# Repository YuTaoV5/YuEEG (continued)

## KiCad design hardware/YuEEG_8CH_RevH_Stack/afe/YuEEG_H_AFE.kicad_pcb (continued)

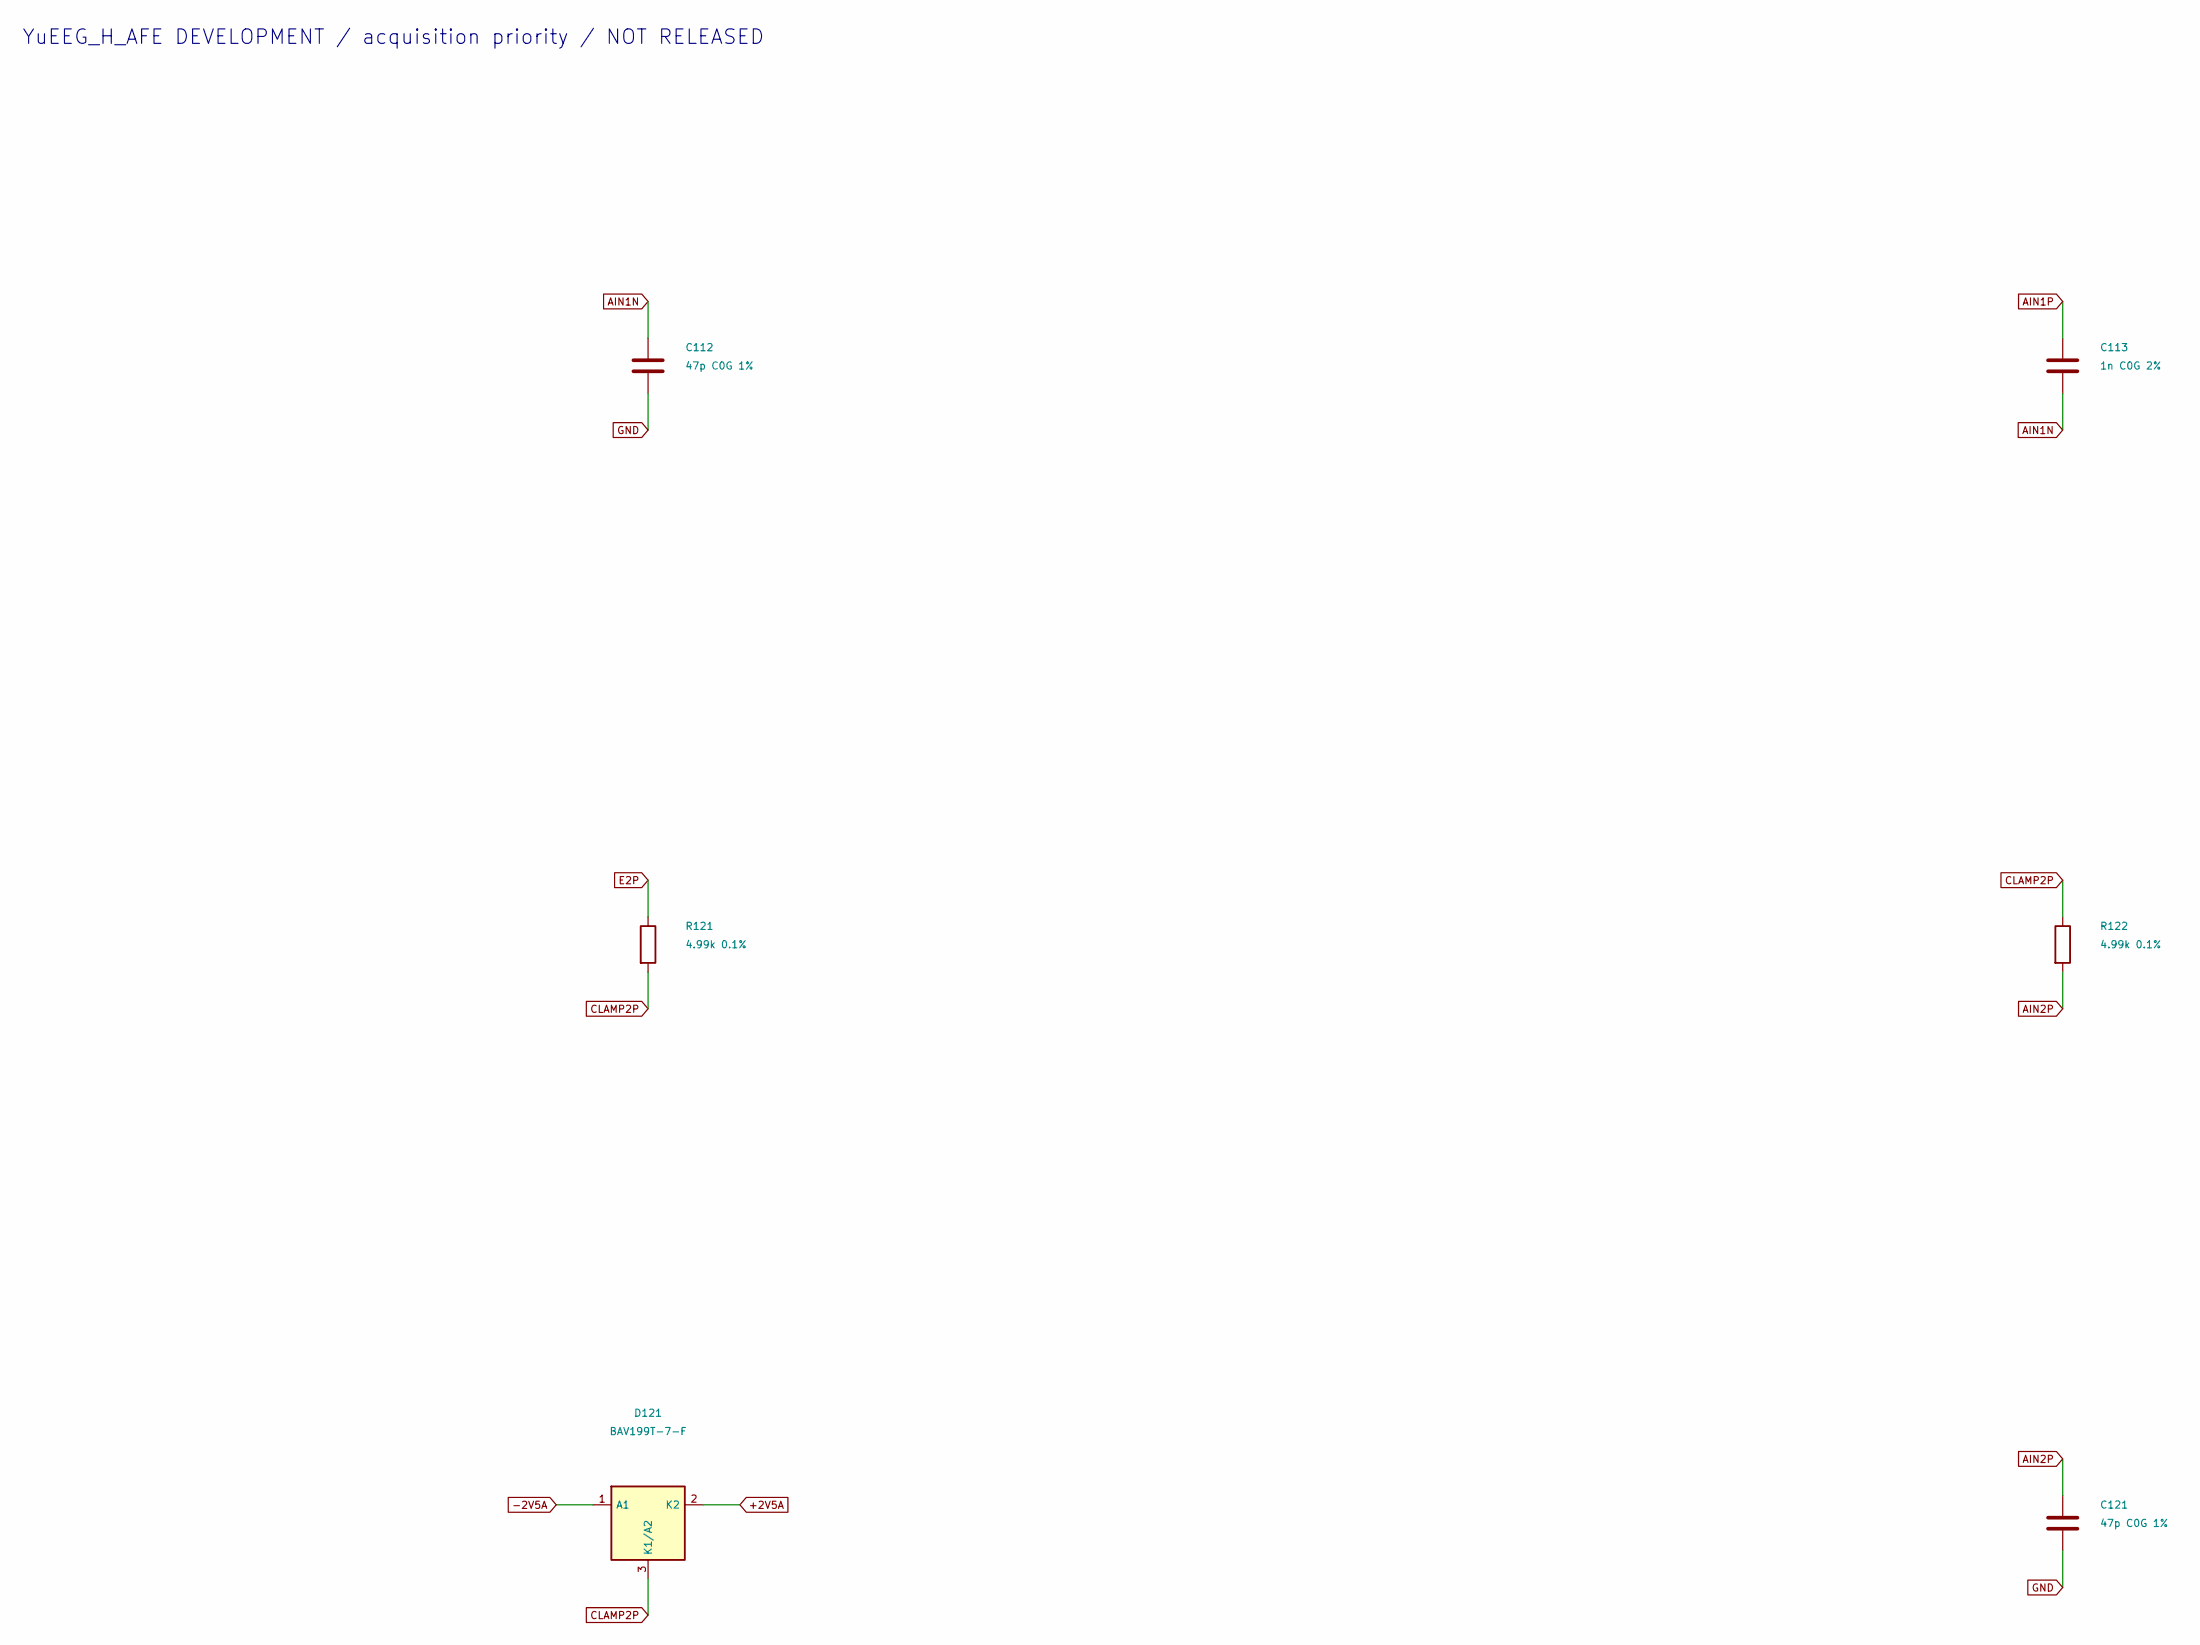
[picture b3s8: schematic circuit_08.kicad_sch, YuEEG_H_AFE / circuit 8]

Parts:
C112, C121: 47p C0G 1%; C_0402_1005Metric
C113: 1n C0G 2%; C_0402_1005Metric
D121: BAV199T-7-F; SOT-523
R121, R122: 4.99k 0.1%; R_0402_1005Metric

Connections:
+2V5A: D121.2 (K2); also elsewhere on the board
-2V5A: D121.1 (A1); also elsewhere on the board
AIN1N: C112.1, C113.2; also elsewhere on the board
AIN1P: C113.1; also elsewhere on the board
AIN2P: C121.1, R122.2; also elsewhere on the board
CLAMP2P: D121.3 (K1/A2), R121.2, R122.1
E2P: R121.1; also elsewhere on the board
GND: C112.2, C121.2; also elsewhere on the board

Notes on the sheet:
YuEEG_H_AFE DEVELOPMENT / acquisition priority / NOT RELEASED

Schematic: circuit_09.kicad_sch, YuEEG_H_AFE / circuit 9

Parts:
C122: 47p C0G 1%; C_0402_1005Metric
C123: 1n C0G 2%; C_0402_1005Metric
D122: BAV199T-7-F; SOT-523
R123, R124, R131: 4.99k 0.1%; R_0402_1005Metric

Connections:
+2V5A: D122.2 (K2); also elsewhere on the board
-2V5A: D122.1 (A1); also elsewhere on the board
AIN2N: C122.1, C123.2, R124.2; also elsewhere on the board
AIN2P: C123.1; also elsewhere on the board
CLAMP2N: D122.3 (K1/A2), R123.2, R124.1
CLAMP3P: R131.2; also elsewhere on the board
E3P: R131.1; also elsewhere on the board
GND: C122.2; also elsewhere on the board
REF_RAW: R123.1; also elsewhere on the board

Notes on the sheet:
YuEEG_H_AFE DEVELOPMENT / acquisition priority / NOT RELEASED

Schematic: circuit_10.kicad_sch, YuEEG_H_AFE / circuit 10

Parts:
C131: 47p C0G 1%; C_0402_1005Metric
D131, D132: BAV199T-7-F; SOT-523
R132, R133, R134: 4.99k 0.1%; R_0402_1005Metric

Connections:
+2V5A: D131.2 (K2), D132.2 (K2); also elsewhere on the board
-2V5A: D131.1 (A1), D132.1 (A1); also elsewhere on the board
AIN3N: R134.2; also elsewhere on the board
AIN3P: C131.1, R132.2; also elsewhere on the board
CLAMP3N: D132.3 (K1/A2), R133.2, R134.1
CLAMP3P: D131.3 (K1/A2), R132.1; also elsewhere on the board
GND: C131.2; also elsewhere on the board
REF_RAW: R133.1; also elsewhere on the board

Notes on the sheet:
YuEEG_H_AFE DEVELOPMENT / acquisition priority / NOT RELEASED

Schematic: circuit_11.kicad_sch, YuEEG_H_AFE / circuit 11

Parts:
C132, C141: 47p C0G 1%; C_0402_1005Metric
C133: 1n C0G 2%; C_0402_1005Metric
D141: BAV199T-7-F; SOT-523
R141, R142: 4.99k 0.1%; R_0402_1005Metric

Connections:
+2V5A: D141.2 (K2); also elsewhere on the board
-2V5A: D141.1 (A1); also elsewhere on the board
AIN3N: C132.1, C133.2; also elsewhere on the board
AIN3P: C133.1; also elsewhere on the board
AIN4P: C141.1, R142.2; also elsewhere on the board
CLAMP4P: D141.3 (K1/A2), R141.2, R142.1
E4P: R141.1; also elsewhere on the board
GND: C132.2, C141.2; also elsewhere on the board

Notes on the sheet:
YuEEG_H_AFE DEVELOPMENT / acquisition priority / NOT RELEASED

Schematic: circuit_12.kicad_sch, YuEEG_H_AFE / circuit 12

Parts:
C142: 47p C0G 1%; C_0402_1005Metric
C143: 1n C0G 2%; C_0402_1005Metric
D142: BAV199T-7-F; SOT-523
R143, R144, R151: 4.99k 0.1%; R_0402_1005Metric

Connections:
+2V5A: D142.2 (K2); also elsewhere on the board
-2V5A: D142.1 (A1); also elsewhere on the board
AIN4N: C142.1, C143.2, R144.2; also elsewhere on the board
AIN4P: C143.1; also elsewhere on the board
CLAMP4N: D142.3 (K1/A2), R143.2, R144.1
CLAMP5P: R151.2; also elsewhere on the board
E5P: R151.1; also elsewhere on the board
GND: C142.2; also elsewhere on the board
REF_RAW: R143.1; also elsewhere on the board

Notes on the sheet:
YuEEG_H_AFE DEVELOPMENT / acquisition priority / NOT RELEASED

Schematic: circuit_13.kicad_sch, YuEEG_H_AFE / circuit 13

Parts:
C151: 47p C0G 1%; C_0402_1005Metric
D151, D152: BAV199T-7-F; SOT-523
R152, R153, R154: 4.99k 0.1%; R_0402_1005Metric

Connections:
+2V5A: D151.2 (K2), D152.2 (K2); also elsewhere on the board
-2V5A: D151.1 (A1), D152.1 (A1); also elsewhere on the board
AIN5N: R154.2; also elsewhere on the board
AIN5P: C151.1, R152.2; also elsewhere on the board
CLAMP5N: D152.3 (K1/A2), R153.2, R154.1
CLAMP5P: D151.3 (K1/A2), R152.1; also elsewhere on the board
GND: C151.2; also elsewhere on the board
REF_RAW: R153.1; also elsewhere on the board

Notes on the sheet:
YuEEG_H_AFE DEVELOPMENT / acquisition priority / NOT RELEASED

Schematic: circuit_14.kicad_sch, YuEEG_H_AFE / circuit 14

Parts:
C152, C161: 47p C0G 1%; C_0402_1005Metric
C153: 1n C0G 2%; C_0402_1005Metric
D161: BAV199T-7-F; SOT-523
R161, R162: 4.99k 0.1%; R_0402_1005Metric

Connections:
+2V5A: D161.2 (K2); also elsewhere on the board
-2V5A: D161.1 (A1); also elsewhere on the board
AIN5N: C152.1, C153.2; also elsewhere on the board
AIN5P: C153.1; also elsewhere on the board
AIN6P: C161.1, R162.2; also elsewhere on the board
CLAMP6P: D161.3 (K1/A2), R161.2, R162.1
E6P: R161.1; also elsewhere on the board
GND: C152.2, C161.2; also elsewhere on the board

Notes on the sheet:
YuEEG_H_AFE DEVELOPMENT / acquisition priority / NOT RELEASED

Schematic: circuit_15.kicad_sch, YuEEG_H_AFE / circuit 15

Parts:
C162: 47p C0G 1%; C_0402_1005Metric
C163: 1n C0G 2%; C_0402_1005Metric
D162: BAV199T-7-F; SOT-523
R163, R164, R171: 4.99k 0.1%; R_0402_1005Metric

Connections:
+2V5A: D162.2 (K2); also elsewhere on the board
-2V5A: D162.1 (A1); also elsewhere on the board
AIN6N: C162.1, C163.2, R164.2; also elsewhere on the board
AIN6P: C163.1; also elsewhere on the board
CLAMP6N: D162.3 (K1/A2), R163.2, R164.1
CLAMP7P: R171.2; also elsewhere on the board
E7P: R171.1; also elsewhere on the board
GND: C162.2; also elsewhere on the board
REF_RAW: R163.1; also elsewhere on the board

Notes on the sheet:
YuEEG_H_AFE DEVELOPMENT / acquisition priority / NOT RELEASED

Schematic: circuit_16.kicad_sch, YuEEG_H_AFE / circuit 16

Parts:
C171: 47p C0G 1%; C_0402_1005Metric
D171, D172: BAV199T-7-F; SOT-523
R172, R173, R174: 4.99k 0.1%; R_0402_1005Metric

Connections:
+2V5A: D171.2 (K2), D172.2 (K2); also elsewhere on the board
-2V5A: D171.1 (A1), D172.1 (A1); also elsewhere on the board
AIN7N: R174.2; also elsewhere on the board
AIN7P: C171.1, R172.2; also elsewhere on the board
CLAMP7N: D172.3 (K1/A2), R173.2, R174.1
CLAMP7P: D171.3 (K1/A2), R172.1; also elsewhere on the board
GND: C171.2; also elsewhere on the board
REF_RAW: R173.1; also elsewhere on the board

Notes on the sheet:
YuEEG_H_AFE DEVELOPMENT / acquisition priority / NOT RELEASED

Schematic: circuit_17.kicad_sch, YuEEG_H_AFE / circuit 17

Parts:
C172, C181: 47p C0G 1%; C_0402_1005Metric
C173: 1n C0G 2%; C_0402_1005Metric
D181: BAV199T-7-F; SOT-523
R181, R182: 4.99k 0.1%; R_0402_1005Metric

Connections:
+2V5A: D181.2 (K2); also elsewhere on the board
-2V5A: D181.1 (A1); also elsewhere on the board
AIN7N: C172.1, C173.2; also elsewhere on the board
AIN7P: C173.1; also elsewhere on the board
AIN8P: C181.1, R182.2; also elsewhere on the board
CLAMP8P: D181.3 (K1/A2), R181.2, R182.1
E8P: R181.1; also elsewhere on the board
GND: C172.2, C181.2; also elsewhere on the board

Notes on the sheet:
YuEEG_H_AFE DEVELOPMENT / acquisition priority / NOT RELEASED

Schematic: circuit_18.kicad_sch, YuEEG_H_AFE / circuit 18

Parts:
C182: 47p C0G 1%; C_0402_1005Metric
C183: 1n C0G 2%; C_0402_1005Metric
C401: 22u 25V X7R; C_1206_3216Metric
D182: BAV199T-7-F; SOT-523
R183, R184: 4.99k 0.1%; R_0402_1005Metric

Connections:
+2V5A: D182.2 (K2); also elsewhere on the board
-2V5A: D182.1 (A1); also elsewhere on the board
AIN8N: C182.1, C183.2, R184.2; also elsewhere on the board
AIN8P: C183.1; also elsewhere on the board
CLAMP8N: D182.3 (K1/A2), R183.2, R184.1
GND: C182.2, C401.2; also elsewhere on the board
REF_RAW: R183.1; also elsewhere on the board
SYS_5V: C401.1; also elsewhere on the board

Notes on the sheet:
YuEEG_H_AFE DEVELOPMENT / acquisition priority / NOT RELEASED

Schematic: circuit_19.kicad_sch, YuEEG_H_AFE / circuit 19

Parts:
C402: 22u 25V X7R; C_1206_3216Metric
C403, C404: 10n C0G; C_0402_1005Metric
R401: 27.4k 0.1%; R_0402_1005Metric
R402: 10k 0.1%; R_0402_1005Metric
U401: TPS7A4901DGNR; HVSSOP-8-1EP_3x3mm_P0.65mm_EP1.57x1.89mm

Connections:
+4V4_PRE: C404.1, R401.1, U401.1 (OUT); also elsewhere on the board
GND: C402.2, C403.2, R402.2, U401.4 (GND), U401.9 (EP); also elsewhere on the board
LDO_FB: C404.2, R401.2, R402.1, U401.2 (FB)
LDO_NR: C403.1, U401.6 (NR/SS)
SYS_5V: C402.1, U401.5 (EN), U401.8 (IN); also elsewhere on the board

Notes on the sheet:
YuEEG_H_AFE DEVELOPMENT / acquisition priority / NOT RELEASED

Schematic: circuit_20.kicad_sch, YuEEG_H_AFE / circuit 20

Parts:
C405: 22u 16V X7R MSASE31LBB7226MTNA01; TY_MSASE31LBB7226MTNA01_1206
C410: 1u 10V X7R; C_0603_1608Metric
C411: 10n C0G; C_0402_1005Metric
D403: BAT46W pre-LDO reverse bypass; D_SOD-123
TP403: +4V4_PRE; TestPoint_Pad_D1.5mm
U403: TPS73225DBVR; SOT-23-5

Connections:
+2V5A: U403.5 (OUT); also elsewhere on the board
+4V4_PRE: C405.1, C410.1, D403.2 (A), TP403.1, U403.1 (IN), U403.3 (EN); also elsewhere on the board
GND: C405.2, C410.2, C411.2, U403.2 (GND); also elsewhere on the board
POS_NR: C411.1, U403.4 (NR)
SYS_5V: D403.1 (K); also elsewhere on the board

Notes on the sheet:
YuEEG_H_AFE DEVELOPMENT / acquisition priority / NOT RELEASED

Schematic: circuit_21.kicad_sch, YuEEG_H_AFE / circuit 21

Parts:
C412, C415: 10u 10V X7R; C_0805_2012Metric
C413, C414: 2.2u 10V X7R; C_0805_2012Metric
R410: 4.99k 1%; R_0402_1005Metric
U404: TPS60403DBVR; SOT-23-5

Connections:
+2V5A: C412.1, R410.1; also elsewhere on the board
+4V4_PRE: C413.1, U404.2 (IN); also elsewhere on the board
CFLY_MINUS: C414.2, U404.3 (C_{FLY-})
CFLY_PLUS: C414.1, U404.5 (C_{FLY+})
GND: C412.2, C413.2, C415.1, R410.2, U404.4 (GND); also elsewhere on the board
NEG_RAW: C415.2, U404.1 (OUT); also elsewhere on the board

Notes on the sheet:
YuEEG_H_AFE DEVELOPMENT / acquisition priority / NOT RELEASED

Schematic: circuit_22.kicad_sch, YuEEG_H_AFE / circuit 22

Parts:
C416: 10n C0G; C_0402_1005Metric
C417: 10u 10V X7R; C_0805_2012Metric
D402: BAT46W reverse-current bypass; D_SOD-123
R411: 4.99k 1%; R_0402_1005Metric
TP405: +2V5A; TestPoint_Pad_D1.5mm
U405: TPS72325DBVR; SOT-23-5

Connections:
+2V5A: TP405.1; also elsewhere on the board
+3V3_AFE: U405.3 (EN); also elsewhere on the board
-2V5A: C417.2, D402.1 (K), R411.2, U405.5 (OUT); also elsewhere on the board
GND: C416.2, C417.1, R411.1, U405.1 (GND); also elsewhere on the board
NEG_NR: C416.1, U405.4 (NR)
NEG_RAW: D402.2 (A), U405.2 (IN); also elsewhere on the board

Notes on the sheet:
YuEEG_H_AFE DEVELOPMENT / acquisition priority / NOT RELEASED

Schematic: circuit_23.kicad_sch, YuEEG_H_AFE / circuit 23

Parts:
C418: 1u 10V X7R; C_0603_1608Metric
CH1: 1u 10V; C_0603_1608Metric
CH2: 100n 10V; C_0402_1005Metric
FBH1: 600R@100MHz / verify DCR and current; L_0603_1608Metric
TP406: -2V5A; TestPoint_Pad_D1.5mm
TP407: NEG_RAW; TestPoint_Pad_D1.5mm

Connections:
+3V3: FBH1.1; also elsewhere on the board
+3V3_AFE: CH1.1, CH2.1, FBH1.2; also elsewhere on the board
-2V5A: TP406.1; also elsewhere on the board
GND: C418.1, CH1.2, CH2.2; also elsewhere on the board
NEG_RAW: C418.2, TP407.1; also elsewhere on the board

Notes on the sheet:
YuEEG_H_AFE DEVELOPMENT / acquisition priority / NOT RELEASED

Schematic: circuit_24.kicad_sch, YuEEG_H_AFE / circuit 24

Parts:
JH1: SGDBF-08-020P-H45 / SMT BTB; SGD_BF08_020_H45_Logical

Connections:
+3V3: JH1.3; also elsewhere on the board
ADS_CS: JH1.9; also elsewhere on the board
ADS_DRDY: JH1.13; also elsewhere on the board
ADS_MISO: JH1.11; also elsewhere on the board
ADS_MOSI: JH1.7; also elsewhere on the board
ADS_PWDN: JH1.16; also elsewhere on the board
ADS_RESET: JH1.15; also elsewhere on the board
ADS_SCLK: JH1.5; also elsewhere on the board
ADS_START: JH1.17; also elsewhere on the board
GND: JH1.2, JH1.4, JH1.6, JH1.8, JH1.10, JH1.12, JH1.14, JH1.18, JH1.20; also elsewhere on the board
SYS_5V: JH1.1, JH1.19; also elsewhere on the board

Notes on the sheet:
YuEEG_H_AFE DEVELOPMENT / acquisition priority / NOT RELEASED

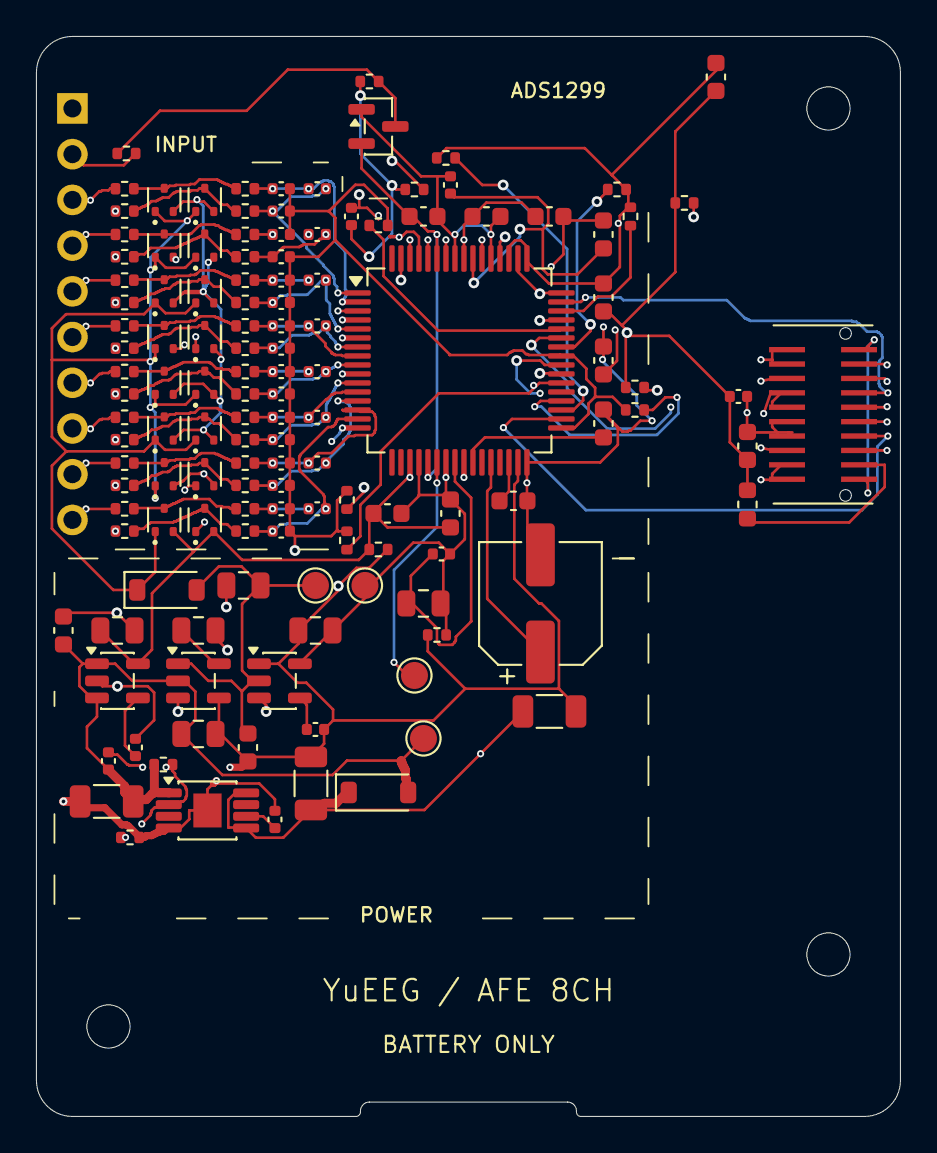
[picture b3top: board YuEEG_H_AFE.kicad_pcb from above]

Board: 4 copper layers, 48.0 x 60.0 mm, 138 parts (0 on the bottom side), 77 nets.

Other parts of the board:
H1, H2, H3: M2 NYLON ONLY; MountingHole_M2_Routed_2p4

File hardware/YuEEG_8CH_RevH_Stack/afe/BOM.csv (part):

Reference,Value,Footprint,Sheet,Datasheet
U1,ADS1299PAG,Package_QFP:TQFP-64_10x10mm_P0.5mm,circuit_01,https://www.ti.com/lit/ds/symlink/ads1299.pdf
R201,10k,Resistor_SMD:R_0402_1005Metric,circuit_01,~
R202,10k,Resistor_SMD:R_0402_1005Metric,circuit_02,~
R203,10k,Resistor_SMD:R_0402_1005Metric,circuit_02,~
R204,10k,Resistor_SMD:R_0402_1005Metric,circuit_02,~
R205,10k,Resistor_SMD:R_0402_1005Metric,circuit_02,~
R206,10k,Resistor_SMD:R_0402_1005Metric,circuit_02,~
R207,10k,Resistor_SMD:R_0402_1005Metric,circuit_02,~
R208,10k,Resistor_SMD:R_0402_1005Metric,circuit_03,~
R209,10k,Resistor_SMD:R_0402_1005Metric,circuit_03,~
R210,1M 1%,Resistor_SMD:R_0402_1005Metric,circuit_03,~
C201,1.5n C0G,Capacitor_SMD:C_0402_1005Metric,circuit_03,~
R211,499k 1%,Resistor_SMD:R_0402_1005Metric,circuit_03,~
R212,499k 1%,Resistor_SMD:R_0402_1005Metric,circuit_03,~
C202,10u 10V X7R,Capacitor_SMD:C_0805_2012Metric,circuit_04,~
C203,100n 10V,Capacitor_SMD:C_0402_1005Metric,circuit_04,~
C210,1u 10V X7R,Capacitor_SMD:C_0603_1608Metric,circuit_04,~
C211,1u 10V X7R,Capacitor_SMD:C_0603_1608Metric,circuit_04,~
C212,1u 10V X7R,Capacitor_SMD:C_0603_1608Metric,circuit_04,~
C213,1u 10V X7R,Capacitor_SMD:C_0603_1608Metric,circuit_04,~
C214,1u 10V X7R,Capacitor_SMD:C_0603_1608Metric,circuit_05,~
C215,1u 10V X7R,Capacitor_SMD:C_0603_1608Metric,circuit_05,~
C216,1u 10V X7R,Capacitor_SMD:C_0603_1608Metric,circuit_05,~
C217,1u 10V X7R,Capacitor_SMD:C_0603_1608Metric,circuit_05,~
C220,100u 25V EEEFT1E101AP H5.8,Capacitor_SMD:CP_Elec_6.3x5.8,circuit_05,~
C221,1u 10V,Capacitor_SMD:C_0603_1608Metric,circuit_05,~
C222,1u 10V,Capacitor_SMD:C_0603_1608Metric,circuit_06,~
C223,100n 10V,Capacitor_SMD:C_0402_1005Metric,circuit_06,~
C224,1u 10V,Capacitor_SMD:C_0603_1608Metric,circuit_06,~
D801,BAV199 BIAS CLAMP,Package_TO_SOT_SMD:SOT-23,circuit_06,https://assets.nexperia.com/documents/data-sheet/BAV199.pdf
J1301,1x10 2.54mm RIGHT ANGLE / ELECTRODES,YuEEG:Electrode_1x10_Horizontal_ReverseLogical,circuit_06,~
R111,4.99k 0.1%,Resistor_SMD:R_0402_1005Metric,circuit_06,~
R112,4.99k 0.1%,Resistor_SMD:R_0402_1005Metric,circuit_07,~
D111,BAV199T-7-F,Package_TO_SOT_SMD:SOT-523,circuit_07,https://assets.nexperia.com/documents/data-sheet/BAV199.pdf
C111,47p C0G 1%,Capacitor_SMD:C_0402_1005Metric,circuit_07,~
R113,4.99k 0.1%,Resistor_SMD:R_0402_1005Metric,circuit_07,~
R114,4.99k 0.1%,Resistor_SMD:R_0402_1005Metric,circuit_07,~
D112,BAV199T-7-F,Package_TO_SOT_SMD:SOT-523,circuit_07,https://assets.nexperia.com/documents/data-sheet/BAV199.pdf
C112,47p C0G 1%,Capacitor_SMD:C_0402_1005Metric,circuit_08,~
C113,1n C0G 2%,Capacitor_SMD:C_0402_1005Metric,circuit_08,~
R121,4.99k 0.1%,Resistor_SMD:R_0402_1005Metric,circuit_08,~
R122,4.99k 0.1%,Resistor_SMD:R_0402_1005Metric,circuit_08,~
D121,BAV199T-7-F,Package_TO_SOT_SMD:SOT-523,circuit_08,https://assets.nexperia.com/documents/data-sheet/BAV199.pdf
C121,47p C0G 1%,Capacitor_SMD:C_0402_1005Metric,circuit_08,~
R123,4.99k 0.1%,Resistor_SMD:R_0402_1005Metric,circuit_09,~
R124,4.99k 0.1%,Resistor_SMD:R_0402_1005Metric,circuit_09,~
D122,BAV199T-7-F,Package_TO_SOT_SMD:SOT-523,circuit_09,https://assets.nexperia.com/documents/data-sheet/BAV199.pdf
C122,47p C0G 1%,Capacitor_SMD:C_0402_1005Metric,circuit_09,~
C123,1n C0G 2%,Capacitor_SMD:C_0402_1005Metric,circuit_09,~
R131,4.99k 0.1%,Resistor_SMD:R_0402_1005Metric,circuit_09,~
R132,4.99k 0.1%,Resistor_SMD:R_0402_1005Metric,circuit_10,~
D131,BAV199T-7-F,Package_TO_SOT_SMD:SOT-523,circuit_10,https://assets.nexperia.com/documents/data-sheet/BAV199.pdf
C131,47p C0G 1%,Capacitor_SMD:C_0402_1005Metric,circuit_10,~
R133,4.99k 0.1%,Resistor_SMD:R_0402_1005Metric,circuit_10,~
R134,4.99k 0.1%,Resistor_SMD:R_0402_1005Metric,circuit_10,~
D132,BAV199T-7-F,Package_TO_SOT_SMD:SOT-523,circuit_10,https://assets.nexperia.com/documents/data-sheet/BAV199.pdf
C132,47p C0G 1%,Capacitor_SMD:C_0402_1005Metric,circuit_11,~
C133,1n C0G 2%,Capacitor_SMD:C_0402_1005Metric,circuit_11,~
R141,4.99k 0.1%,Resistor_SMD:R_0402_1005Metric,circuit_11,~
R142,4.99k 0.1%,Resistor_SMD:R_0402_1005Metric,circuit_11,~
D141,BAV199T-7-F,Package_TO_SOT_SMD:SOT-523,circuit_11,https://assets.nexperia.com/documents/data-sheet/BAV199.pdf
C141,47p C0G 1%,Capacitor_SMD:C_0402_1005Metric,circuit_11,~
R143,4.99k 0.1%,Resistor_SMD:R_0402_1005Metric,circuit_12,~
R144,4.99k 0.1%,Resistor_SMD:R_0402_1005Metric,circuit_12,~
D142,BAV199T-7-F,Package_TO_SOT_SMD:SOT-523,circuit_12,https://assets.nexperia.com/documents/data-sheet/BAV199.pdf
C142,47p C0G 1%,Capacitor_SMD:C_0402_1005Metric,circuit_12,~
C143,1n C0G 2%,Capacitor_SMD:C_0402_1005Metric,circuit_12,~
R151,4.99k 0.1%,Resistor_SMD:R_0402_1005Metric,circuit_12,~
R152,4.99k 0.1%,Resistor_SMD:R_0402_1005Metric,circuit_13,~
D151,BAV199T-7-F,Package_TO_SOT_SMD:SOT-523,circuit_13,https://assets.nexperia.com/documents/data-sheet/BAV199.pdf
C151,47p C0G 1%,Capacitor_SMD:C_0402_1005Metric,circuit_13,~
R153,4.99k 0.1%,Resistor_SMD:R_0402_1005Metric,circuit_13,~
R154,4.99k 0.1%,Resistor_SMD:R_0402_1005Metric,circuit_13,~
D152,BAV199T-7-F,Package_TO_SOT_SMD:SOT-523,circuit_13,https://assets.nexperia.com/documents/data-sheet/BAV199.pdf
C152,47p C0G 1%,Capacitor_SMD:C_0402_1005Metric,circuit_14,~
C153,1n C0G 2%,Capacitor_SMD:C_0402_1005Metric,circuit_14,~
R161,4.99k 0.1%,Resistor_SMD:R_0402_1005Metric,circuit_14,~
R162,4.99k 0.1%,Resistor_SMD:R_0402_1005Metric,circuit_14,~
D161,BAV199T-7-F,Package_TO_SOT_SMD:SOT-523,circuit_14,https://assets.nexperia.com/documents/data-sheet/BAV199.pdf
C161,47p C0G 1%,Capacitor_SMD:C_0402_1005Metric,circuit_14,~
R163,4.99k 0.1%,Resistor_SMD:R_0402_1005Metric,circuit_15,~
R164,4.99k 0.1%,Resistor_SMD:R_0402_1005Metric,circuit_15,~
D162,BAV199T-7-F,Package_TO_SOT_SMD:SOT-523,circuit_15,https://assets.nexperia.com/documents/data-sheet/BAV199.pdf
C162,47p C0G 1%,Capacitor_SMD:C_0402_1005Metric,circuit_15,~
C163,1n C0G 2%,Capacitor_SMD:C_0402_1005Metric,circuit_15,~
R171,4.99k 0.1%,Resistor_SMD:R_0402_1005Metric,circuit_15,~
R172,4.99k 0.1%,Resistor_SMD:R_0402_1005Metric,circuit_16,~
D171,BAV199T-7-F,Package_TO_SOT_SMD:SOT-523,circuit_16,https://assets.nexperia.com/documents/data-sheet/BAV199.pdf
C171,47p C0G 1%,Capacitor_SMD:C_0402_1005Metric,circuit_16,~
R173,4.99k 0.1%,Resistor_SMD:R_0402_1005Metric,circuit_16,~
R174,4.99k 0.1%,Resistor_SMD:R_0402_1005Metric,circuit_16,~
D172,BAV199T-7-F,Package_TO_SOT_SMD:SOT-523,circuit_16,https://assets.nexperia.com/documents/data-sheet/BAV199.pdf
C172,47p C0G 1%,Capacitor_SMD:C_0402_1005Metric,circuit_17,~
C173,1n C0G 2%,Capacitor_SMD:C_0402_1005Metric,circuit_17,~
R181,4.99k 0.1%,Resistor_SMD:R_0402_1005Metric,circuit_17,~
R182,4.99k 0.1%,Resistor_SMD:R_0402_1005Metric,circuit_17,~
D181,BAV199T-7-F,Package_TO_SOT_SMD:SOT-523,circuit_17,https://assets.nexperia.com/documents/data-sheet/BAV199.pdf
C181,47p C0G 1%,Capacitor_SMD:C_0402_1005Metric,circuit_17,~
R183,4.99k 0.1%,Resistor_SMD:R_0402_1005Metric,circuit_18,~
R184,4.99k 0.1%,Resistor_SMD:R_0402_1005Metric,circuit_18,~
D182,BAV199T-7-F,Package_TO_SOT_SMD:SOT-523,circuit_18,https://assets.nexperia.com/documents/data-sheet/BAV199.pdf
C182,47p C0G 1%,Capacitor_SMD:C_0402_1005Metric,circuit_18,~
C183,1n C0G 2%,Capacitor_SMD:C_0402_1005Metric,circuit_18,~
C401,22u 25V X7R,Capacitor_SMD:C_1206_3216Metric,circuit_18,~
U401,TPS7A4901DGNR,Package_SO:HVSSOP-8-1EP_3x3mm_P0.65mm_EP1.57x1.89mm,circuit_19,https://www.ti.com/lit/gpn/TPS7A49
C402,22u 25V X7R,Capacitor_SMD:C_1206_3216Metric,circuit_19,~
C403,10n C0G,Capacitor_SMD:C_0402_1005Metric,circuit_19,~
R401,27.4k 0.1%,Resistor_SMD:R_0402_1005Metric,circuit_19,~
R402,10k 0.1%,Resistor_SMD:R_0402_1005Metric,circuit_19,~
C404,10n C0G,Capacitor_SMD:C_0402_1005Metric,circuit_19,~
C405,22u 16V X7R MSASE31LBB7226MTNA01,YuEEG:TY_MSASE31LBB7226MTNA01_1206,circuit_20,https://ds.yuden.co.jp/TYCOMPAS/ap/detail?pn=MSASE31LBB7226M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
TP403,+4V4_PRE,TestPoint:TestPoint_Pad_D1.5mm,circuit_20,~
D403,BAT46W pre-LDO reverse bypass,Diode_SMD:D_SOD-123,circuit_20,~
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
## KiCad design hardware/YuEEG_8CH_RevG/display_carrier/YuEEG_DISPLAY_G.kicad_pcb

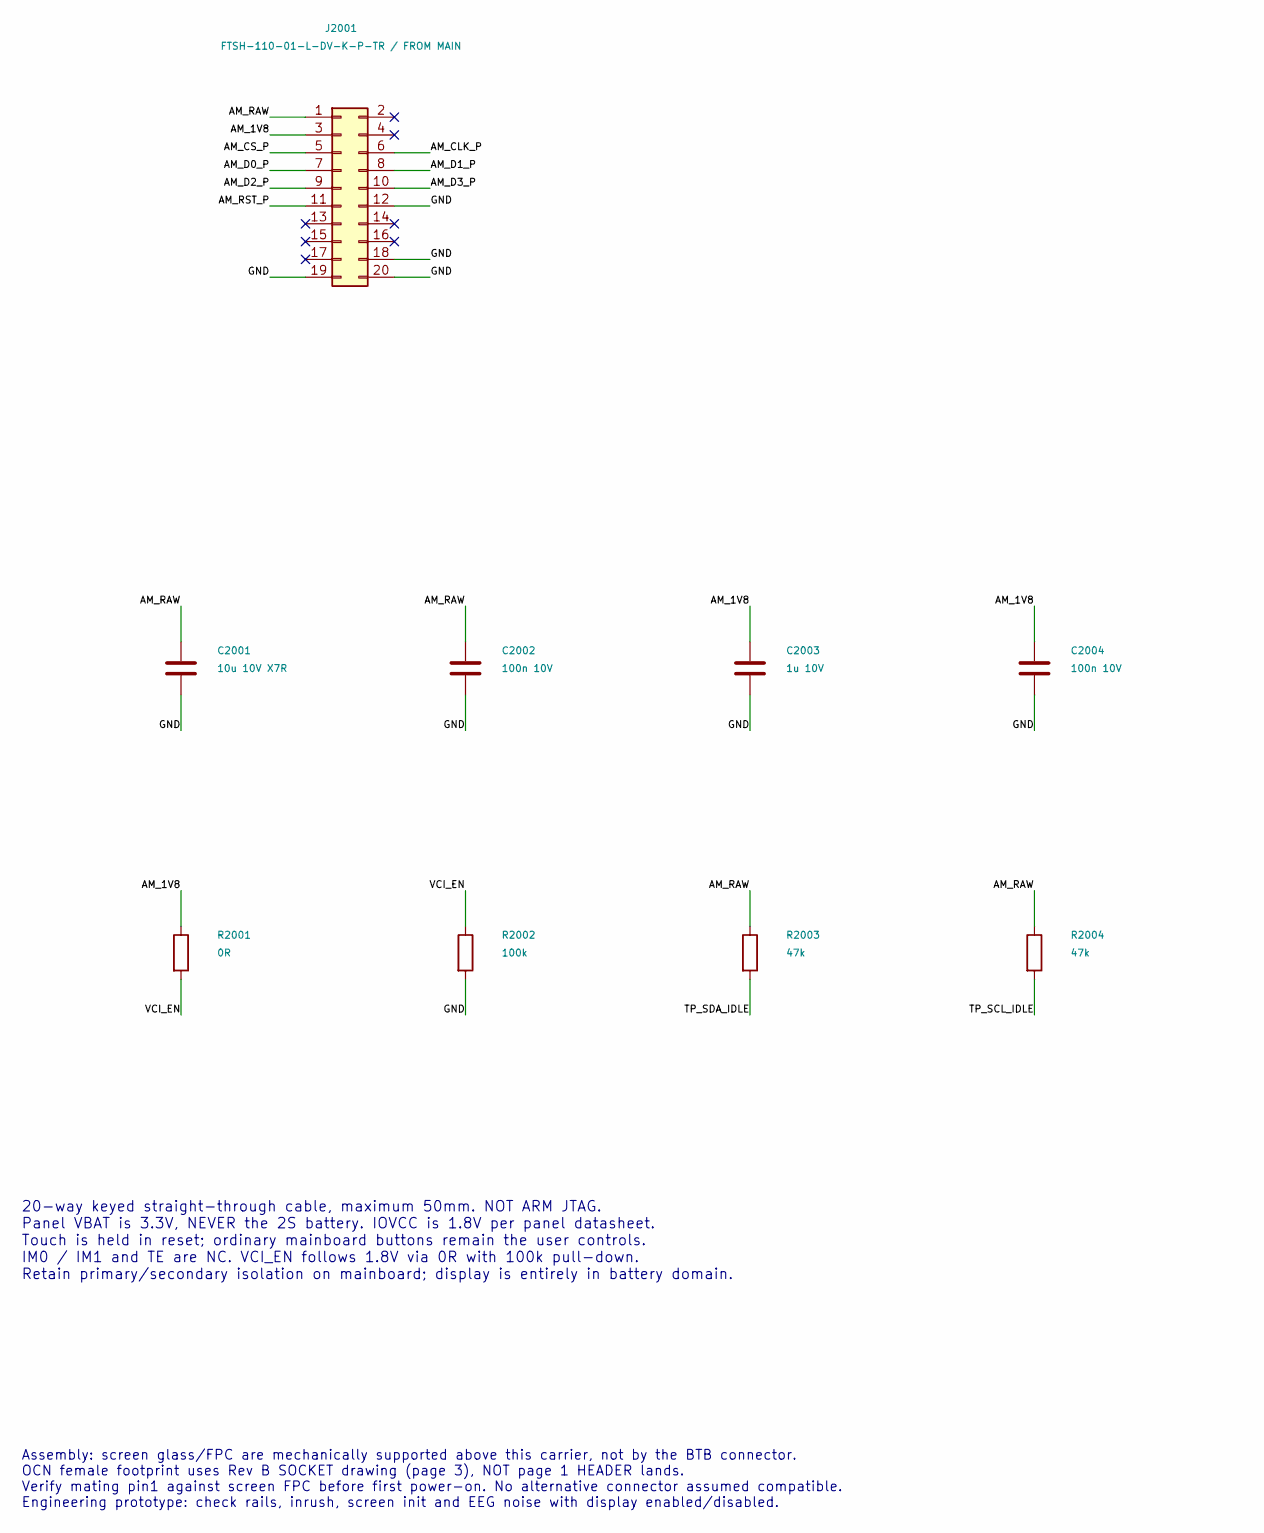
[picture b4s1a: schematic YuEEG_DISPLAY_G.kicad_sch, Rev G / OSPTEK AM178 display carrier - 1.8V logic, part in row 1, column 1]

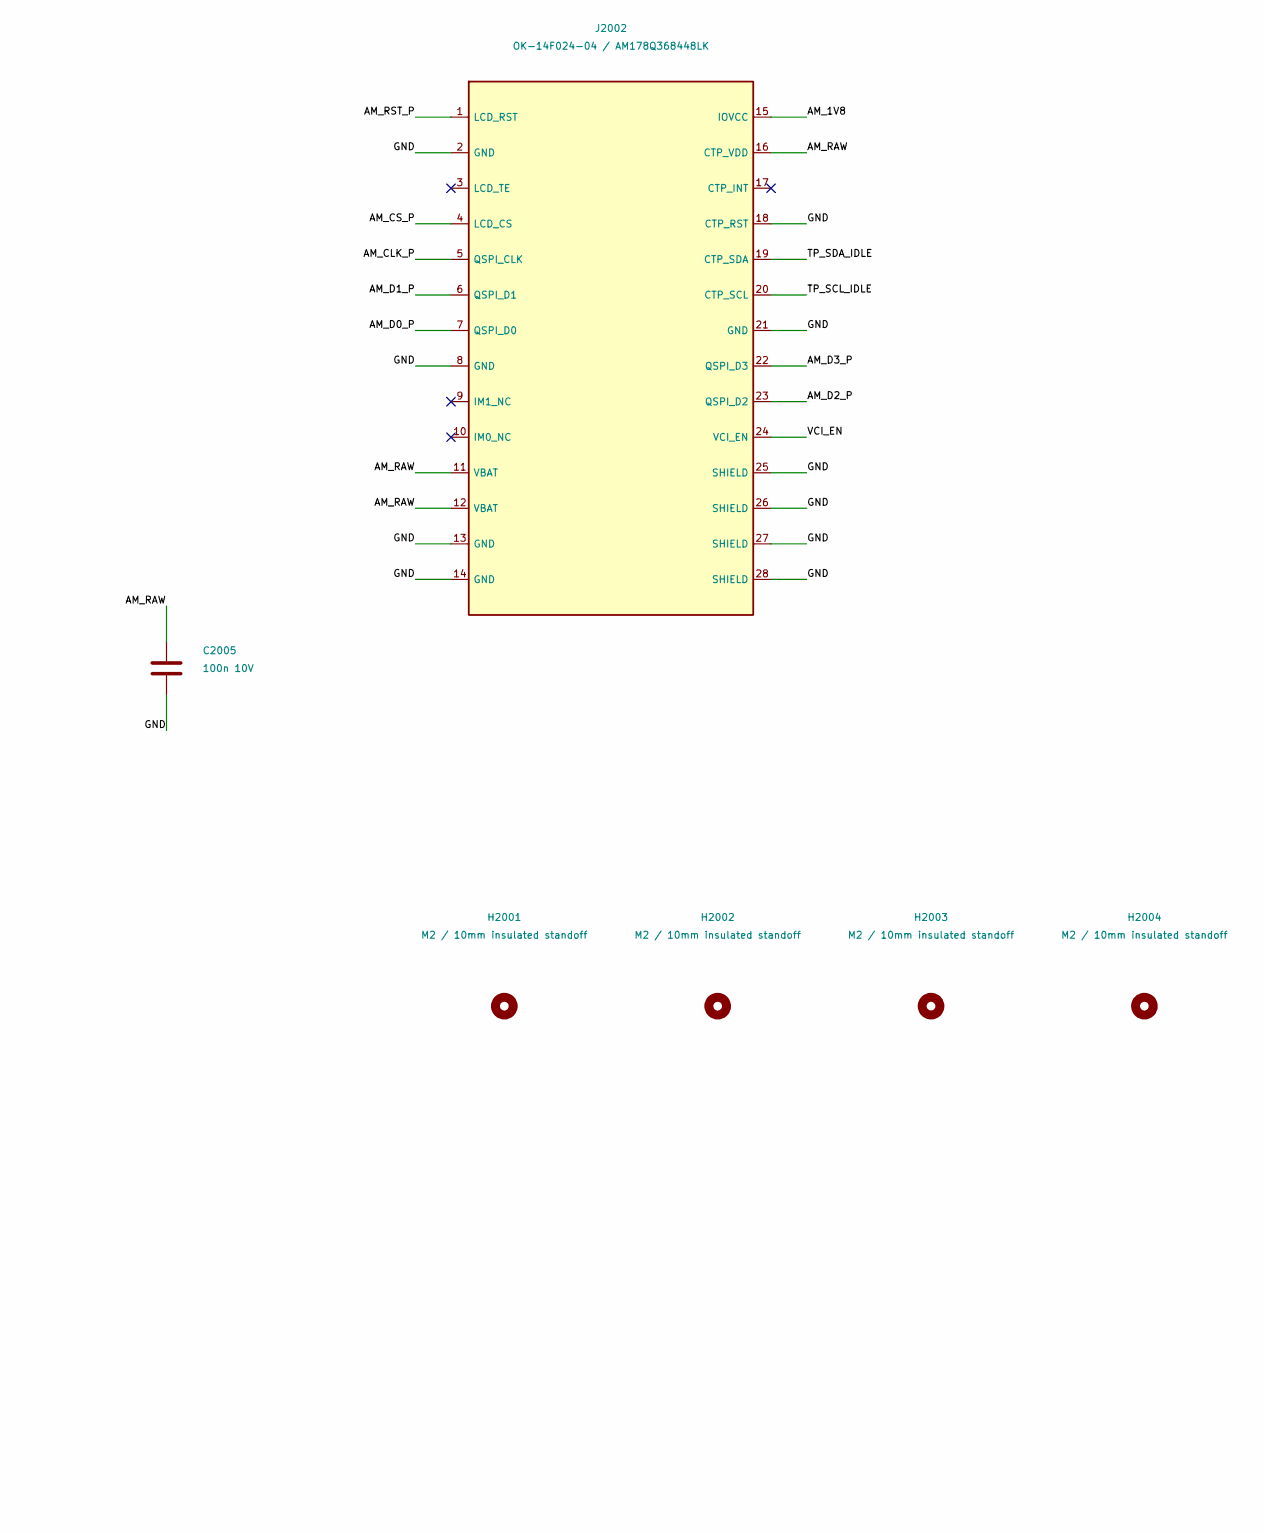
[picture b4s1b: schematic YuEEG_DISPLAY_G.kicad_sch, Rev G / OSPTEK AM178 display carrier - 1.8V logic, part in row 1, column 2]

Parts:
C2001: 10u 10V X7R; C_0603_1608Metric
C2002, C2004, C2005: 100n 10V; C_0603_1608Metric
C2003: 1u 10V; C_0603_1608Metric
H2001, H2002, H2003, H2004: M2 / 10mm insulated standoff; MountingHole_2.2mm_M2
J2001: FTSH-110-01-L-DV-K-P-TR / FROM MAIN; Samtec_FTSH_110_01_L_DV_K_2x10
J2002: OK-14F024-04 / AM178Q368448LK; OCN_OK_14F024_04
R2001: 0R; R_0603_1608Metric
R2002: 100k; R_0603_1608Metric
R2003, R2004: 47k; R_0603_1608Metric

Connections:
/AM_1V8: C2003.1, C2004.1, J2001.3, J2002.15 (IOVCC), R2001.1
/AM_CLK_P: J2001.6, J2002.5 (QSPI_CLK)
/AM_CS_P: J2001.5, J2002.4 (LCD_CS)
/AM_D0_P: J2001.7, J2002.7 (QSPI_D0)
/AM_D1_P: J2001.8, J2002.6 (QSPI_D1)
/AM_D2_P: J2001.9, J2002.23 (QSPI_D2)
/AM_D3_P: J2001.10, J2002.22 (QSPI_D3)
/AM_RAW: C2001.1, C2002.1, C2005.1, J2001.1, J2002.11 (VBAT), J2002.12 (VBAT), J2002.16 (CTP_VDD), R2003.1, R2004.1
/AM_RST_P: J2001.11, J2002.1 (LCD_RST)
/GND: C2001.2, C2002.2, C2003.2, C2004.2, C2005.2, J2001.12, J2001.18, J2001.19, J2001.20, J2002.2 (GND), J2002.8 (GND), J2002.13 (GND), J2002.14 (GND), J2002.18 (CTP_RST), J2002.21 (GND), J2002.25 (SHIELD), J2002.26 (SHIELD), J2002.27 (SHIELD), J2002.28 (SHIELD), R2002.2
/TP_SCL_IDLE: J2002.20 (CTP_SCL), R2004.2
/TP_SDA_IDLE: J2002.19 (CTP_SDA), R2003.2
/VCI_EN: J2002.24 (VCI_EN), R2001.2, R2002.1

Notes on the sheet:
20-way keyed straight-through cable, maximum 50mm. NOT ARM JTAG. Panel VBAT is 3.3V, NEVER the 2S battery. IOVCC is 1.8V per panel datasheet. Touch is held in reset; ordinary mainboard buttons remain the user controls. IM0 / IM1 and TE are NC. VCI_EN follows 1.8V via 0R with 100k pull-down. Retain 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
Assembly: screen glass/FPC are mechanically supported above this carrier, not by the BTB connector. OCN female footprint uses Rev B SOCKET drawing (page 3), NOT page 1 HEADER lands. Verify mating pin1 against screen FPC before first power-on. No alternative connector assumed compatible. Engineering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

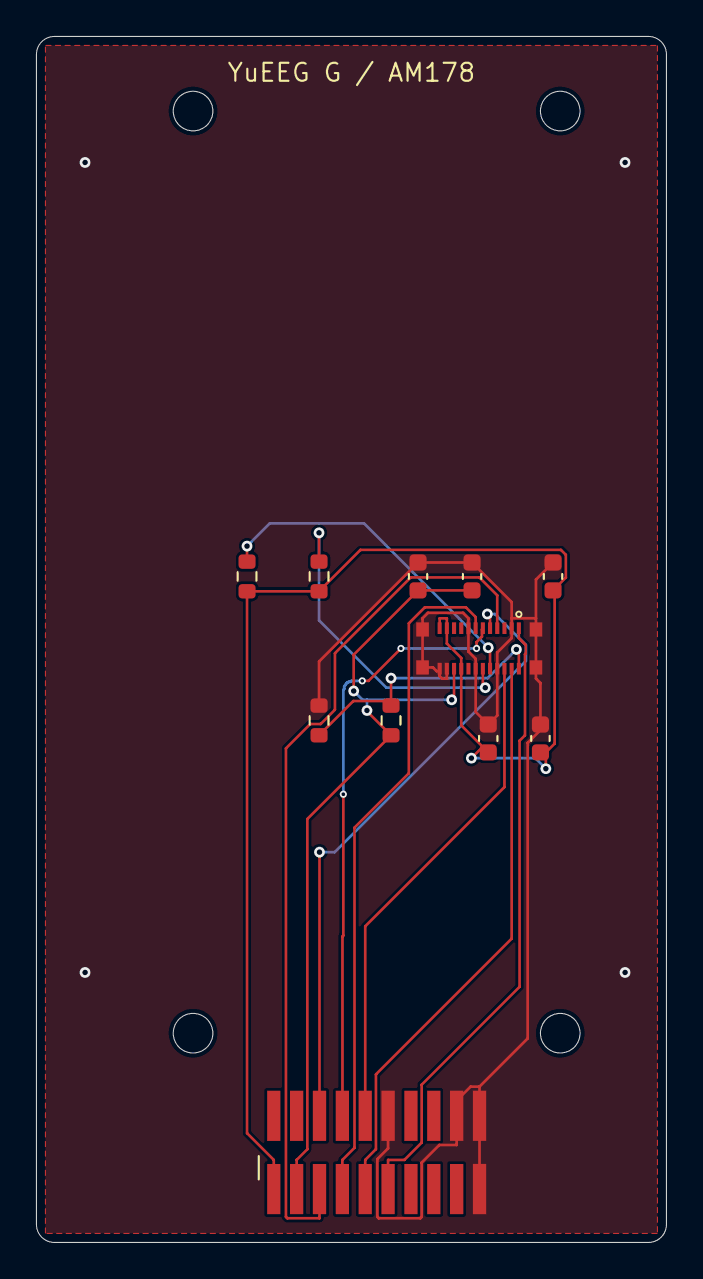
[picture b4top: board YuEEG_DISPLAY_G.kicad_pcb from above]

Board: 2 copper layers, 35.0 x 67.0 mm, 15 parts (0 on the bottom side), 13 nets.

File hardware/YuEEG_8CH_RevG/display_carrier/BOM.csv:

Reference,Value,Footprint,Sheet,Datasheet
J2001,FTSH-110-01-L-DV-K-P-TR / FROM MAIN,YuEEG:Samtec_FTSH_110_01_L_DV_K_2x10,YuEEG_DISPLAY_G,~
J2002,OK-14F024-04 / AM178Q368448LK,YuEEG:OCN_OK_14F024_04,YuEEG_DISPLAY_G,../../../display-amoled-1.78inch-368x448-main/versions/AM178Q368448LK/cad/OK-14F024-04.pdf
C2001,10u 10V X7R,Capacitor_SMD:C_0603_1608Metric,YuEEG_DISPLAY_G,~
C2002,100n 10V,Capacitor_SMD:C_0603_1608Metric,YuEEG_DISPLAY_G,~
C2003,1u 10V,Capacitor_SMD:C_0603_1608Metric,YuEEG_DISPLAY_G,~
C2004,100n 10V,Capacitor_SMD:C_0603_1608Metric,YuEEG_DISPLAY_G,~
C2005,100n 10V,Capacitor_SMD:C_0603_1608Metric,YuEEG_DISPLAY_G,~
R2001,0R,Resistor_SMD:R_0603_1608Metric,YuEEG_DISPLAY_G,~
R2002,100k,Resistor_SMD:R_0603_1608Metric,YuEEG_DISPLAY_G,~
R2003,47k,Resistor_SMD:R_0603_1608Metric,YuEEG_DISPLAY_G,~
R2004,47k,Resistor_SMD:R_0603_1608Metric,YuEEG_DISPLAY_G,~
H2001,M2 / 10mm insulated standoff,MountingHole:MountingHole_2.2mm_M2,YuEEG_DISPLAY_G,~
H2002,M2 / 10mm insulated standoff,MountingHole:MountingHole_2.2mm_M2,YuEEG_DISPLAY_G,~
H2003,M2 / 10mm insulated standoff,MountingHole:MountingHole_2.2mm_M2,YuEEG_DISPLAY_G,~
H2004,M2 / 10mm insulated standoff,MountingHole:MountingHole_2.2mm_M2,YuEEG_DISPLAY_G,~
